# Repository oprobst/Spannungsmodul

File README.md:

# Spannungsversorgungsmodul

Microcontroller based toggle to supply other modules with power.

  * The start time can be configured by a timer. 
  * Low voltage monitoring
  * Provide 5V stabilized and supply voltage to 3rd party modules
  * Timer and voltage visualization by LED

## Usage

When connected to power, the module will start to delivery a stabilized 5V and the supply voltage to a 3rd party component after a configured amount of time.

### Start timer configuration

The module start in status OFF. When initializing it send an switch-off signal to the relay to ensure status.

When the module is connected to power, it waits a few seconds for user input (defined by constant SEC_TILL_ON, default is 10 sec). Every button operation in OFF mode will increase this wait time. When the button is pushed less than 1 sec, the wait time will be increased by StartupTimer#SMALL_TIMER_VALUE (default = 10min). When pushed longer than a second, it will be increased by StartupTimer#BIG_TIMER_VALUE (default = 60min). This time is calculated based on the initial start-up of the module (first connectivity with supply voltage).
The current wait time is visualized by the status LED: Long blink interval means a big waiting duration, short blink interval means that the system waits a complete small timer duration until it starts. A very short flash signals end of wait time visualization. This will apply every 15 seconds when waiting in OFF mode.

When the wait time is exposed, the system will signal two times short-long blinking. Then it activates the mosfet transistors.
It changes to status ON.

### Voltage monitoring
Within this status, the system visualizes every 15 seconds the current voltage measurement. According to the Jumper JP4, it measures the distance from full battery to 9V or 6V (2 or 3 cell LiPo Battery) cut-off voltage. The maximum voltage is not defined by software, a zener diode will restrict it and protect the ADC. Actually, the maximum voltage is defined by hardware and is somewhere around 30V (depending on DCDC converter).

The voltage will be visualized by the flashing LED. The more often the LED flashes, the longer is the distance from current voltage to cut-off voltage. 

When voltage reaches the cut-off voltage (defined by main#ADC_TRESHOLD, default = 660), the LED will fast flash for a around 3 seconds and then initialize the shutdown procedure. Next, the module will visualize the shut-down by two seconds of long-sort LED blinking. Afterwards the relay, as well as the mosfet, will be triggered off. On low voltage shutdown, the microcontroller will be send to power saving sleep mode (SLEEP_MODE_PWR_DOWN). This can only be reverted, when turning supply voltage off and on again (reset).

When the button is pushed during ON mode, she shutdown procedure will also activated. In opposite to the voltage cut-off, this will not trigger a power saving sleep mode. But all timers (including startup-time) will be reset and the system is in OFF mode. Then everything starts again.

## Set-up

Once started, it activates the transistors toggling input voltage to the target system. Maximum current is 5 ampere (depending on mosfet).

In addition, it provides a PIN output for a 5V DCDC converted voltage. Maximum current is restricted to 1 ampere (depending on DCDC Converter).

To protect the battery, a low voltage detection for 3s (12.6V to 9.2V) and 2s (8.4V to 6V) LiPo batteries is available. This is configured by the jumper.

(_For newest schematic, please check the original eagle files!_)

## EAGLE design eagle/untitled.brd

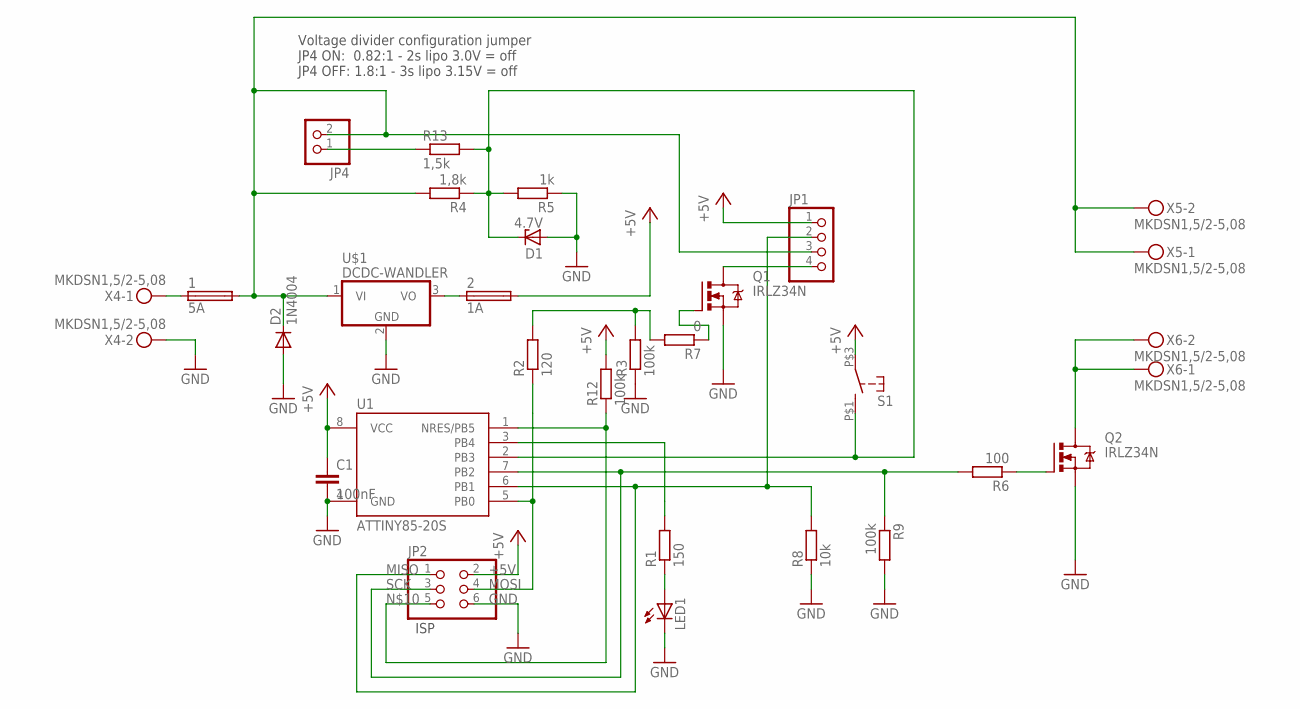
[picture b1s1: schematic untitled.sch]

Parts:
1: 5A; SH22,5A
2: 1A; SH22,5A
C1: 100nF; C0805
D1: 4.7V; SOT23
D2: 1N4004; DO41-10
JP1: PINHD-1X4; 1X04
JP2: PINHD-2X3; 2X03
JP4: PINHD-1X2; 1X02
LED1: LED3MM
Q1, Q2: IRLZ34N; TO220BH
R1: 150; R1206
R2: 120; R1206
R3, R9, R12: 100k; R1206
R4: 1,8k; R1206
R5: 1k; R1206
R6: 100; R1206
R7: 0; R1206
R8: 10k; R1206
R13: 1,5k; R1206
S1: SCHLIESSER_TASTSCHALTER; NAMAE-JTP-1130
U1: ATTINY85-20S; SOIC8_EIAJ_208MIL
U$1: DCDC-WANDLER; TRACOPOWER-DCDCWANDER-TSR1
X4, X5, X6: MKDSN1,5/2-5,08

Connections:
+5V: 2.2, C1.1, JP1.1, JP2.2, R12.2, S1.P$3 (4), U1.8 (VCC)
GND: C1.2, D1.1 (A), D2.A, JP2.6, LED1.K (C), Q1.S, Q2.S, R3.1, R5.1, R8.1, R9.2, U1.4 (GND), U$1.2 (GND), X4.2
MISO: JP1.2, JP2.1, R8.2, U1.6 (PB1)
MOSI: JP2.4, R2.1, U1.5 (PB0)
unnamed: 1.1, X4.1
unnamed: 1.2, D2.C, JP1.3, JP4.2, R4.2, U$1.1 (VI), X5.1, X5.2
unnamed: Q2.D, X6.1, X6.2
unnamed: Q2.G, R6.1
unnamed: LED1.A, R1.1
unnamed: Q1.G, R7.1
unnamed: R2.2, R3.2, R7.2
unnamed: JP2.5, R12.1, U1.1 (NRES/PB5)
unnamed: R1.2, U1.3 (PB4)
unnamed: JP4.1, R13.1
unnamed: 2.1, U$1.3 (VO)
unnamed: JP1.4, Q1.D
RESET: D1.3 (C), R4.1, R5.2, R13.2, S1.P$1 (3), U1.2 (PB3)
SCK: JP2.3, R6.2, R9.1, U1.7 (PB2)

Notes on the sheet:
Voltage divider configuration jumper JP4 ON: 0.82:1 - 2s lipo 3.0V = off JP4 OFF: 1.8:1 - 3s lipo 3.15V = off
ISP

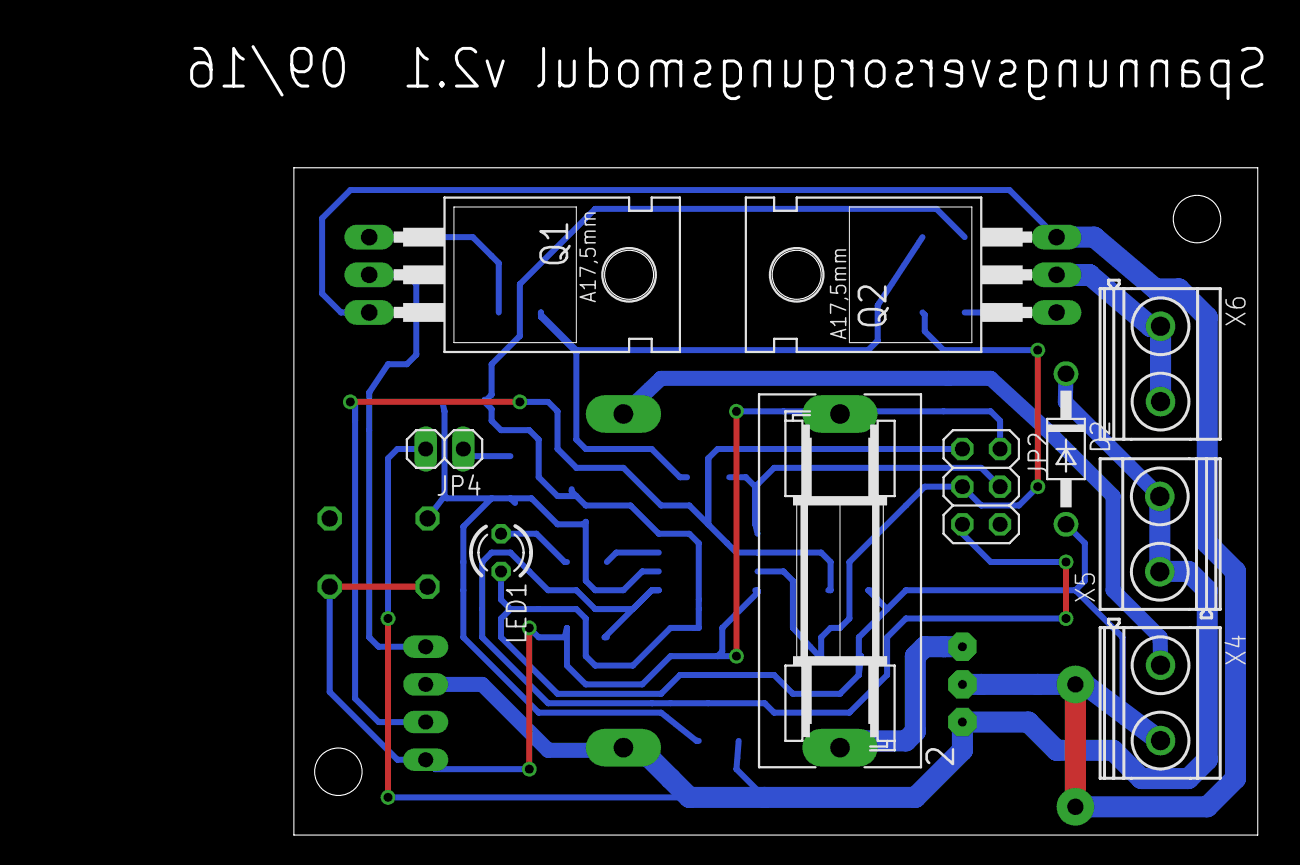
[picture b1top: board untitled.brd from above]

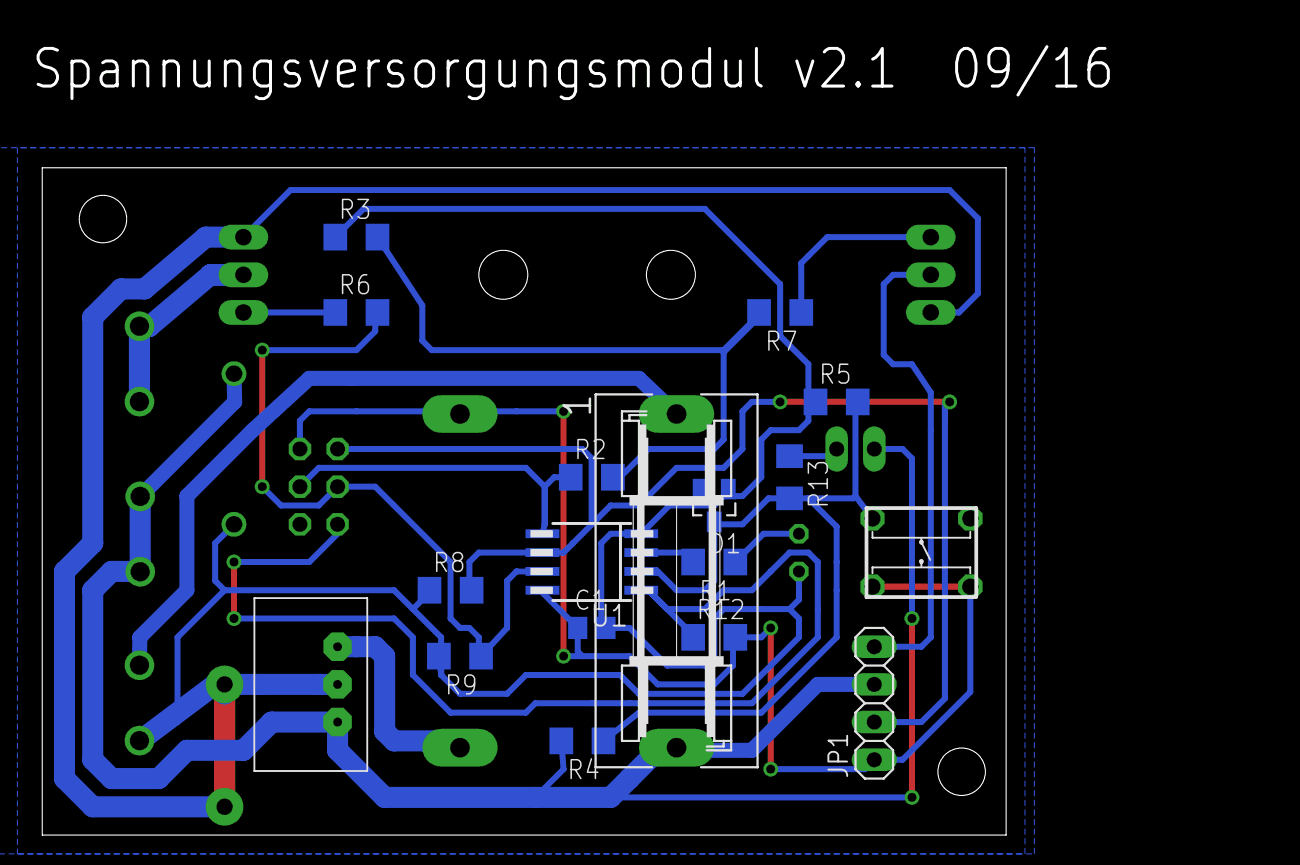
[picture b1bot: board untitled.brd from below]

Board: 2 copper layers, 83.7 x 54.3 mm, 28 parts (18 on the bottom side), 18 nets.

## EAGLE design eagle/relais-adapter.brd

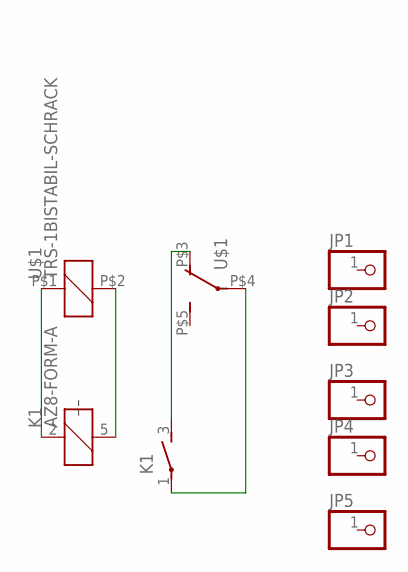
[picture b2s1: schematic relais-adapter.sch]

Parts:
JP1, JP2, JP3, JP4, JP5: PINHD-1X1; 1X01
K1: AZ8-FORM-A; AZ8
U$1: TRS-1BISTABIL-SCHRACK; PRINTRELAIS-SCHRACK-PE-BISTABIL

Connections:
unnamed: K1.2 (1), U$1.P$1 (1)
unnamed: K1.5 (2), U$1.P$2 (2)
unnamed: K1.3 (S), U$1.P$3 (O)
unnamed: K1.1, U$1.P$4

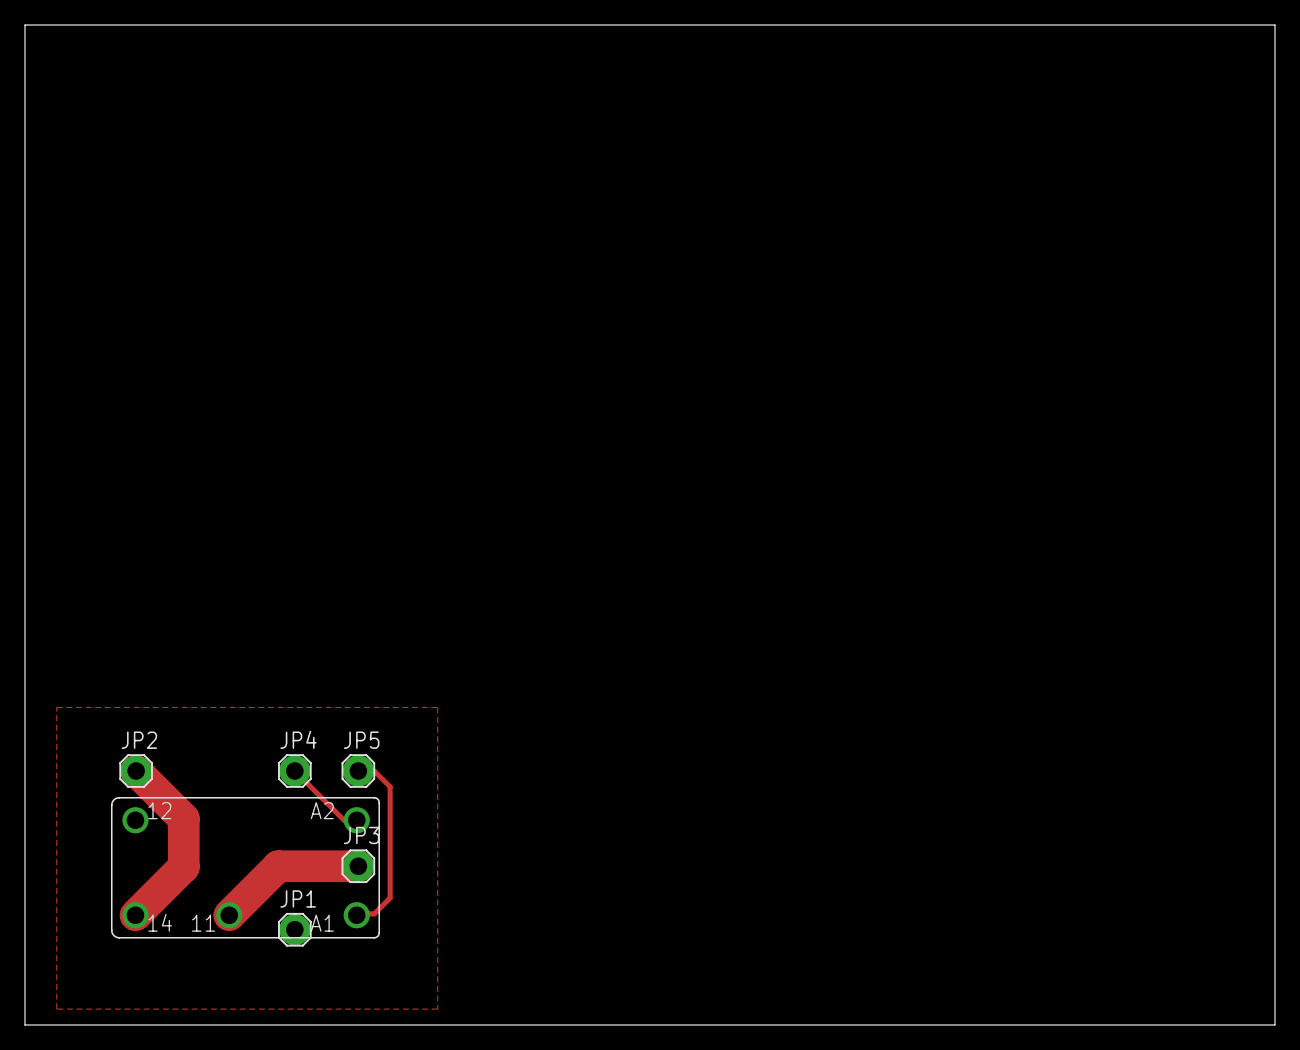
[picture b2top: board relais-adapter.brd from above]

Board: 2 copper layers, 100.0 x 80.0 mm, 7 parts (1 on the bottom side), 4 nets.

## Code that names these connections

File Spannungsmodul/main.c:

#include <avr/io.h>
#include <avr/sleep.h>
#include <util/delay.h>
#include <stdint.h>
#include <avr/interrupt.h>
#include <avr/wdt.h>

#include "VoltageCheck.h"
#include "StartupTimer.h"
#include "PowerSwitch.h"
#include "Stopwatch.h"

#define F_CPU 1000000UL //1 MHz

#define SEC_TILL_ON 10

#define ADC_TRESHOLD 660

#define TRUE 1
#define FALSE 0

/*
 * Main method, will initialize Ports and handle timers, shutdown voltage
 * and button input by user.
 */
int main(void)
{
	
	//out:
	//PB1,PB2 -> Relais
	//PB4 LED
	//PB0 MOSFET
	//in:
	//PB3 ADC for voltage measurement
	DDRB |= ((0 << PB1) |(1 << PB2) |(0 << PB3) |(1 << PB4) | (1 << PB0));
	
	initADC(ADC_TRESHOLD);
	PORTB &= ~(1 << PB2);
	PORTB &= ~(1 << PB0);
	
	PORTB |= (1<<PB4);
	_delay_ms(200);
	PORTB &= ~(1<<PB4);
	_delay_ms(200);
	PORTB |= (1<<PB4);
	_delay_ms(200);
	PORTB &= ~(1<<PB4);
	
	start();
	sei();
	startStopwatch();

	while( 1 ) {
		
		checkForShutdown ();
		
		checkForButton();
		
		if (getSecondsSinceStart() > SEC_TILL_ON){
			if (isOn() == FALSE ){
				checkIfTimeIsOver();
				if ((getSecondsSinceStart() % 15) == 0){
					visualizeTimer(PB4);
				}
			} else {
				sleep ();
			}
		}
		
	}
}

/*
 * Busy waiting. Check button input from time to time.
 * (could be reimplemented by interrupts somewhere in the future...)
 */
void sleep (){
	int8_t i;
	for (i = 0; i < 100; i++){
		checkForButton();
		_delay_ms(100); // 10 sec
		// an interrupt would be more useful here... But anyway, it works.
	}
	visualizeVoltage(PB4);
}

/*
* Check if voltage divider is bridged by switch.
* If longer than 1 sec. pushed, call longButtonPush method, shortButtonPush otherwise.
*/
void checkForButton (void){
	if (readADCsamples(1) > 1000){
		uint8_t i;
		for ( i = 0; i < 10; i++){
			_delay_ms(100);
			if (readADCsamples(3) <= 1000){
				shortButtonPush();
				return;
			}
		}
		longButtonPush();
	}
}

/*
 * Will be called on long button push. Triggers increase of big timer duration.
 * Should also do a reset when system is ON, but this doesn't working...?
 */
void longButtonPush (){
	
	if (isOn()){
		//reset
		wdt_enable(WDTO_15MS);
		for(;;) {}
		} else {
		addBigTimer ();
		visualizeTimer(PB4);
		startStopwatch();
	}
}

/*
 * Short button push was detected. 
 */
void shortButtonPush (){
	
	if (isOn()){
		//shutdown
		startStopwatch();
		resetTimer();
		switchOff();
		
		} else {
		
		addSmallTimer ();
		visualizeTimer(PB4);
		startStopwatch();
	}
}

/*
 * Check if shutdown voltage has been reached.
 * Power down everything in this case.
 */
void checkForShutdown (void){
	
	if (shutdownVoltageReached()){
		cli(); //disable interrupts
		for (uint8_t i = 0; i< 100; i++){
			_delay_ms(35);
			PINB |= (1<<PB4); //Invert PB4
		}		
		switchOff();
		// Go to sleep and only wake up on reset/power switch.		
		PORTB &= ~(1<<PB4); // LED off
		set_sleep_mode(SLEEP_MODE_PWR_DOWN);
		sleep_enable();
		sleep_cpu();
		sleep_disable();
		//here everything should be silent. If we reach the next while loop, something is wrong.
		while (1){
			_delay_ms(1500);
			PINB |= (1<<PB4); //Invert PB4
		}
	}
}
	

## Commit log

2016-01-21 Initial check in
2016-01-21 Added resistor for npn transistors
2016-01-21 Pullup- reset & 2x voltage divider
2016-01-26 Additional jumper for 2s and 3s lipo battery
2016-01-26 First experiments with ADC
2016-01-27 A lot of new code for timer, switch and voltage check
2016-01-27 Changed relais. Fixed compiler failures
2016-01-28 =setup of timer implemented
2016-01-29 added Stopwatch
2016-01-29 exported diagram for readme
2016-01-29 Updated info text in diagram
2016-01-29 Update README.md
    Translated to english and added schematics and explanation of jumpers
2016-01-29 Added list format for connector description
2016-01-29 added H-Bridge hint
2016-02-05 Basic functionality implemented. Lot of fine tuning still needed.
2016-02-06 Adapter from wrong package in V1.1 to V1.2
2016-02-08 Lots of essential changes to functionality
2016-02-09 Close to done. Added correct timer and voltage visualization and calculation
2016-02-09 bugfix low voltage detection
2016-02-10 Added hint about eagle files to the schematic
2016-02-10 Minor bugfixes for timer. Added reset function for restart.
2016-02-15 Added documentation
2016-02-15 Few typo fixes
2016-02-16 Added improvements chapter
2016-02-16 Typo and grammar corrections
2016-09-08 Updated to version 2.1 with mosfets instead of a relay
2016-10-14 Updated schaltplan image
2016-10-14 Updated readme to new version without relay
